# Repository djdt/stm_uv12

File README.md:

# stm_uv12

This repository cotains the kicad files and code for a UVx irradiator designed to fit over a standard 12 well plate.
The controller is powered by a single protected 18650 Li-ion cell, each row of LEDs (3 rows of 4 LEDs) has a R1218x DC/DC converter for control of LED brightness.
Approximate doses (J/m^2) have been calculated using the expected LED outputs and are delivered at a specified rate using the controller.

## PCB Files

UVA_12W_LED_CONTROL: stm32 control board with 16x2 OLED screen (16pin connector).

UVA_12W_LED: board for use with 4x VLMU1610 UVA LEDs.

UVC_12W_LED: board for use with 4x SML-LXF3535UVC UVC LEDs.

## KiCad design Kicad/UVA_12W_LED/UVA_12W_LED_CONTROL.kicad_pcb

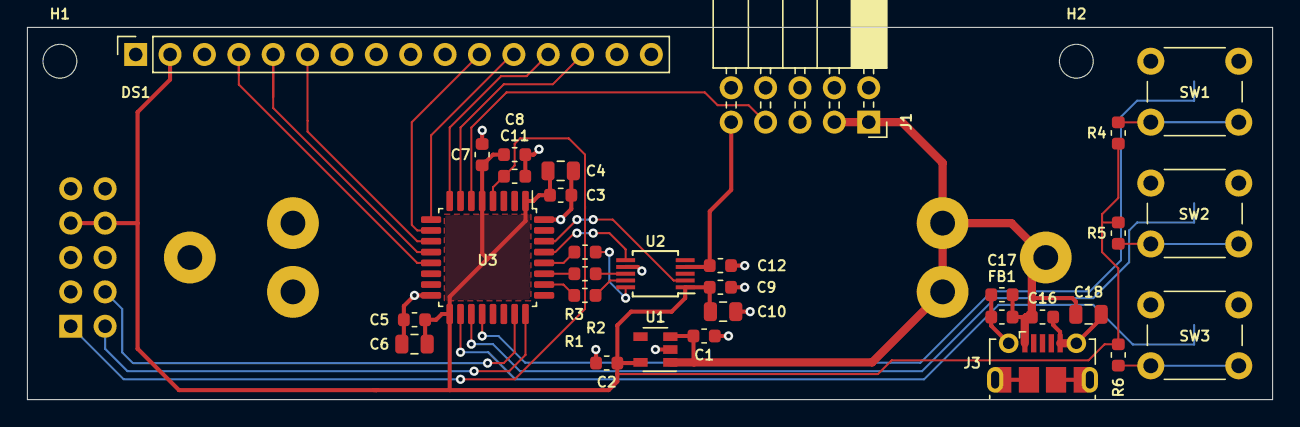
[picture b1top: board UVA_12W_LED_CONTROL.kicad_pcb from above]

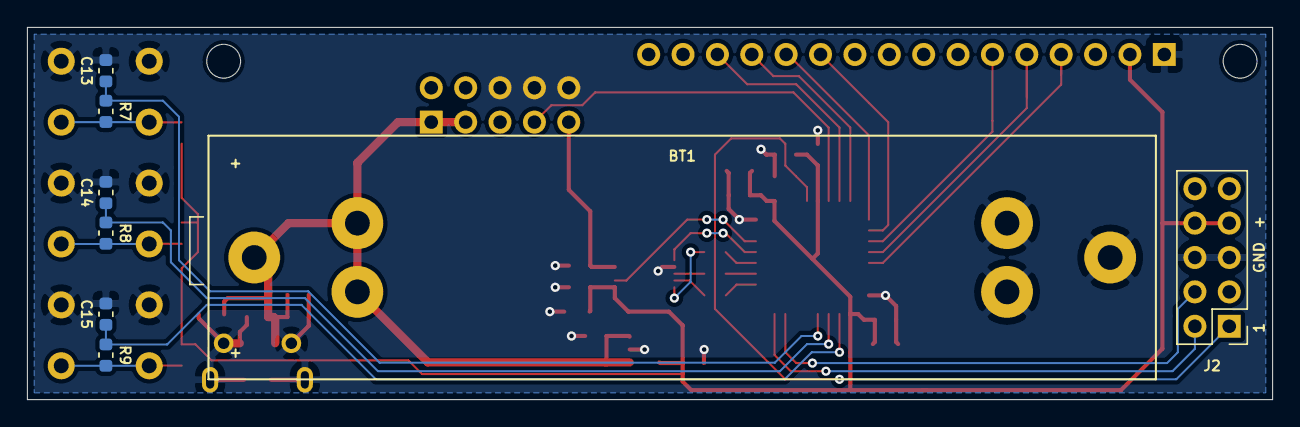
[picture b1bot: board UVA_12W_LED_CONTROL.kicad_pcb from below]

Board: 2 copper layers, 92.0 x 27.5 mm, 41 parts (8 on the bottom side), 29 nets.

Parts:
BT1: Battery; BatteryClip_18mm
C1, C2, C8: 1u; C_0603_1608Metric
C3, C5, C9, C11, C12, C17: 0u1; C_0603_1608Metric
C4, C6: 4u7; C_0805_2012Metric
C7, C13, C14, C15, C16: 10n; C_0603_1608Metric
C10, C18: 10u; C_0805_2012Metric
DS1: OLED-016N002A; PinSocket_1x16_P2.54mm_Vertical
FB1: Ferrite_Bead; L_0603_1608Metric
H1, H2: MountingHole; MountingHole_2.5mm
J1: Conn_02x05_Odd_Even; PinSocket_2x05_P2.54mm_Horizontal
J2: Conn_02x05_Odd_Even; PinHeader_2x05_P2.54mm_Vertical
J3: USB_B_Micro; USB_Micro-B_Molex-105017-0001
R1, R2, R3: 100; R_0603_1608Metric
R4, R5, R6, R7, R8, R9: 10k; R_0603_1608Metric
SW1, SW2, SW3: SW_Push; SW_PUSH_6mm
U1: MSCP1824T; SOT-23-5
U2: MCP48FVBX1; MSOP-10_3x3mm_P0.5mm
U3: STM32F042K6Tx; LQFP-32_7x7mm_P0.8mm

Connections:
/3V3: C2.1, C3.1, C4.1, C5.1, C6.1, C7.1, C8.1, C9.1, C10.1, DS1.2, J2.7, J2.8, R4.1, R5.1, R6.1, U1.5, U2.1, U3.1, U3.5, U3.17
/CS_DAC: U2.2, U3.30
/DB4: DS1.11, U3.10
/DB5: DS1.12, U3.9
/DB6: DS1.13, U3.8
/DB7: DS1.14, U3.7
/Dim: C12.1, J1.9, U2.4
/E: DS1.6, U3.11
/Enable: J1.7, U3.6
/MISO: R3.2, U2.8
/MOSI: R2.2, U3.28
/RS: DS1.4, U3.13
/RST: C11.1, J2.1, U3.4
/R~W: DS1.5, U3.12
/S1: C13.1, R7.1, U3.20
/S2: C14.1, R8.1, U3.19
/S3: C15.1, R9.1, U3.18
/SCLK: R1.2, U3.26
/SWCLK: J2.2, U3.24
/SWDIO: J2.4, U3.23
/Vbat: BT1.1, C1.1, C16.1, C17.1, C18.1, FB1.1, J1.1, J1.3, J3.1, U1.1, U1.3
/~LAT0: U2.6, U3.29
GND: BT1.2, C1.2, C2.2, C3.2, C4.2, C5.2, C6.2, C7.2, C8.2, C9.2, C10.2, C11.2, C12.2, C13.2, C14.2, C15.2, C16.2, C17.2, C18.2, DS1.1, FB1.2, J1.6, J1.8, J1.10, J2.5, J2.6, J3.5, J3.6, SW1.1, SW2.1, SW3.1, U1.2, U2.7, U3.16, U3.32
unnamed: R1.1, U2.9
unnamed: R2.1, U2.10
unnamed: R3.1, U3.27
unnamed: R4.2, R7.2, SW1.2
unnamed: R5.2, R8.2, SW2.2
unnamed: R6.2, R9.2, SW3.2

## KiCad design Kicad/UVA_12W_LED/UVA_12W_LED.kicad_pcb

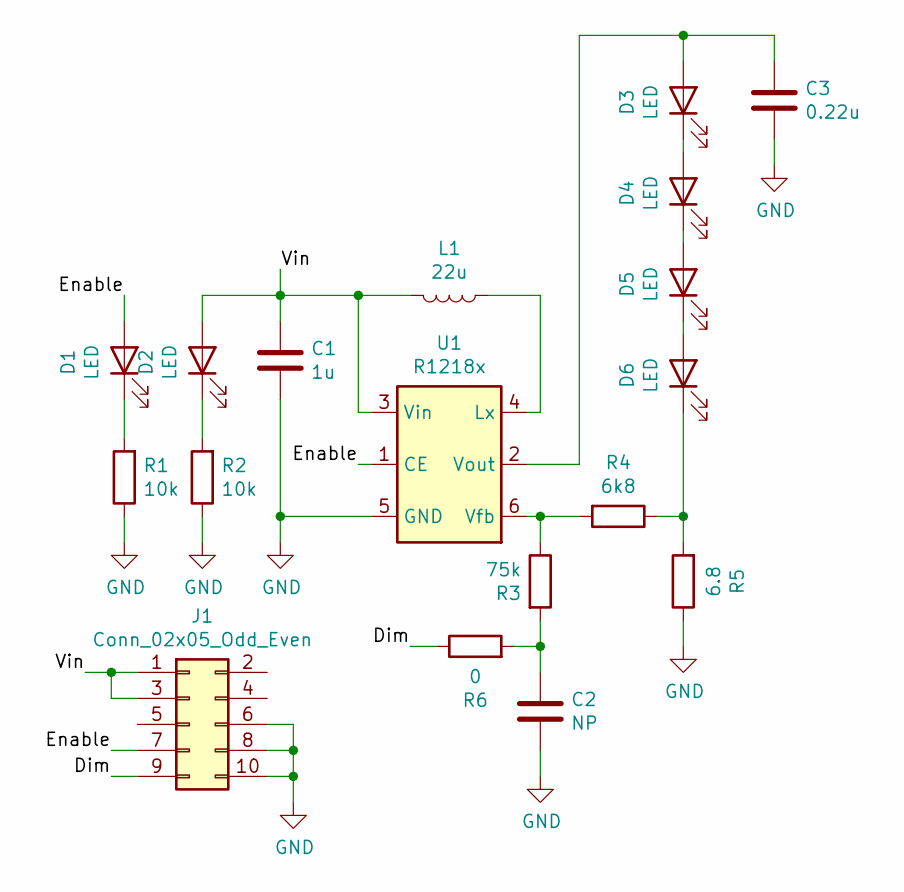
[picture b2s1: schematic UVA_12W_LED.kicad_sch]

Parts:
C1: 1u; C_0603_1608Metric
C2: NP; C_0603_1608Metric
C3: 0.22u; C_0603_1608Metric
D1, D2: LED; LED_0805_2012Metric
D3, D4, D5, D6: LED; VLMU1610
J1: Conn_02x05_Odd_Even; PinSocket_2x05_P2.54mm_Vertical_SMD
L1: 22u; L_0805_2012Metric
R1, R2: 10k; R_0603_1608Metric
R3: 75k; R_0603_1608Metric
R4: 6k8; R_0603_1608Metric
R5: 6.8; R_0603_1608Metric
R6: 0; R_0603_1608Metric
U1: R1218x; SOT-23-6

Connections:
/Dim: J1.9, R6.1
/Enable: D1.2 (A), J1.7, U1.1 (CE)
/Vin: C1.1, D2.2 (A), J1.1, J1.3, L1.2, U1.3 (Vin)
GND: C1.2, C2.2, C3.2, J1.6, J1.8, J1.10, R1.1, R2.1, R5.1, U1.5 (GND)
unnamed: C2.1, R3.2, R6.2
unnamed: C3.1, D3.2 (A), U1.2 (Vout)
unnamed: D1.1 (K), R1.2
unnamed: D2.1 (K), R2.2
unnamed: D3.1 (K), D4.2 (A)
unnamed: D4.1 (K), D5.2 (A)
unnamed: D5.1 (K), D6.2 (A)
unnamed: D6.1 (K), R4.1, R5.2
unnamed: L1.1, U1.4 (Lx)
unnamed: R3.1, R4.2, U1.6 (Vfb)

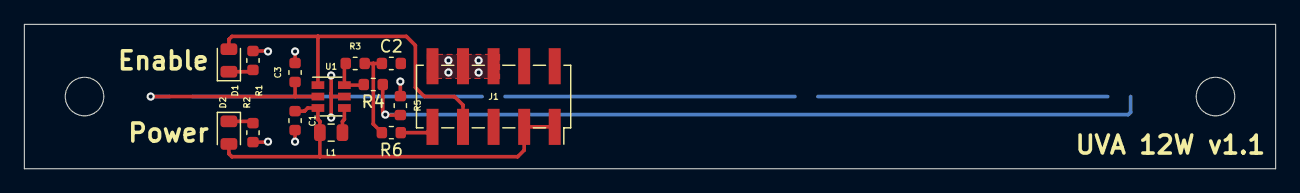
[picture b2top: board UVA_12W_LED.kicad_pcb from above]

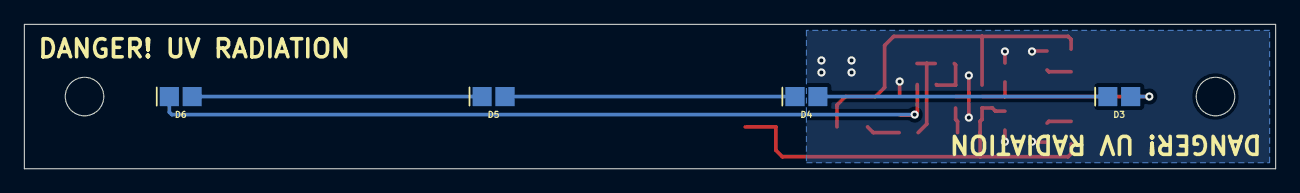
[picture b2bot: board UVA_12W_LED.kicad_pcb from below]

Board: 2 copper layers, 104.0 x 12.0 mm, 18 parts (4 on the bottom side), 14 nets.

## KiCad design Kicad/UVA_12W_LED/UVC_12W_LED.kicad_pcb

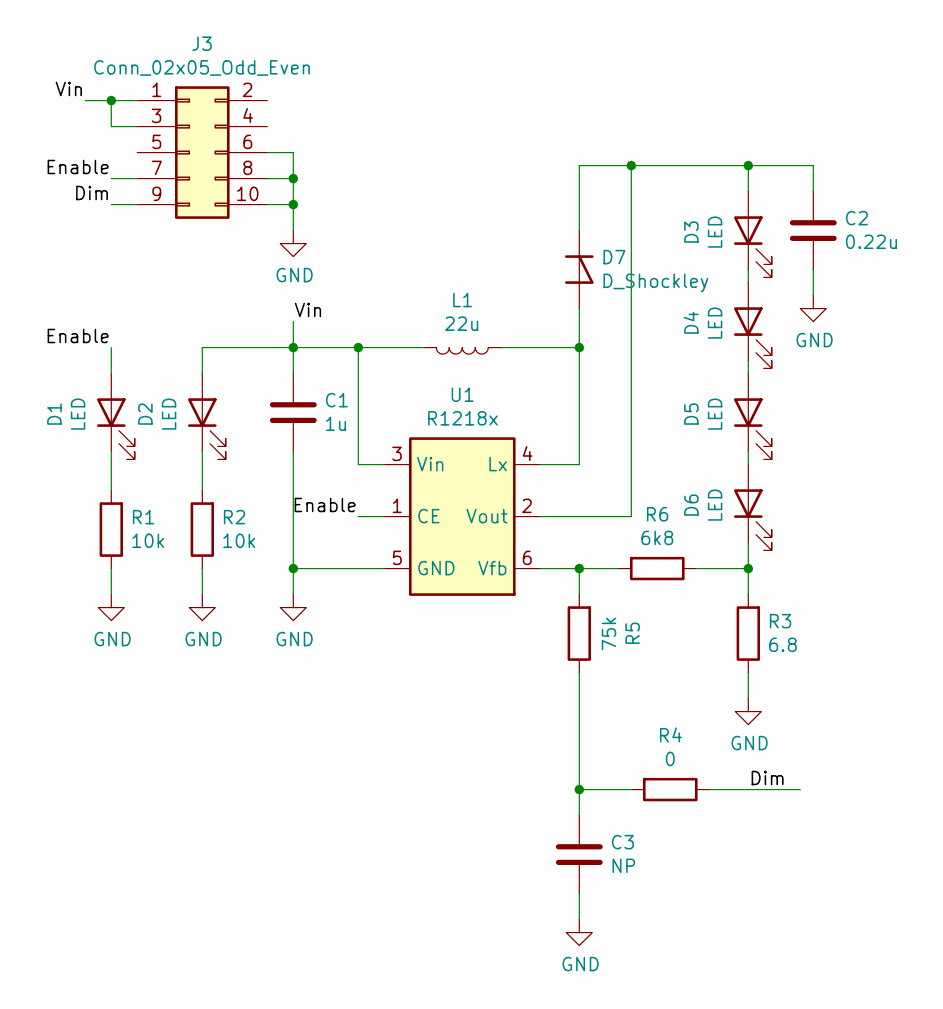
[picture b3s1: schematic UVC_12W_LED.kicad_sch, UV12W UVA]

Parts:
C1: 1u; C_0603_1608Metric
C2: 0.22u; C_0603_1608Metric
C3: NP; C_0603_1608Metric
D1, D2: LED; LED_0805_2012Metric
D3, D4, D5, D6: LED; SML-LXF3535UVC
D7: D_Shockley; D_SOD-123F
J3: Conn_02x05_Odd_Even; PinSocket_2x05_P2.54mm_Vertical_SMD
L1: 22u; L_Taiyo-Yuden_NR-30xx_HandSoldering
R1, R2: 10k; R_0603_1608Metric
R3: 6.8; R_0603_1608Metric
R4: 0; R_0603_1608Metric
R5: 75k; R_0603_1608Metric
R6: 6k8; R_0603_1608Metric
U1: R1218x; SOT-23-6

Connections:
/Dim: J3.9, R4.1
/Enable: D1.2 (A), J3.7, U1.1 (CE)
/Vin: C1.1, D2.2 (A), J3.1, J3.3, L1.2, U1.3 (Vin)
GND: C1.2, C2.2, C3.2, J3.6, J3.8, J3.10, R1.1, R2.1, R3.1, U1.5 (GND)
unnamed: C2.1, D3.2 (A), D7.1 (K), U1.2 (Vout)
unnamed: C3.1, R4.2, R5.1
unnamed: D1.1 (K), R1.2
unnamed: D2.1 (K), R2.2
unnamed: D3.1 (K), D4.2 (A)
unnamed: D4.1 (K), D5.2 (A)
unnamed: D5.1 (K), D6.2 (A)
unnamed: D6.1 (K), R3.2, R6.1
unnamed: D7.2 (A), L1.1, U1.4 (Lx)
unnamed: R5.2, R6.2, U1.6 (Vfb)

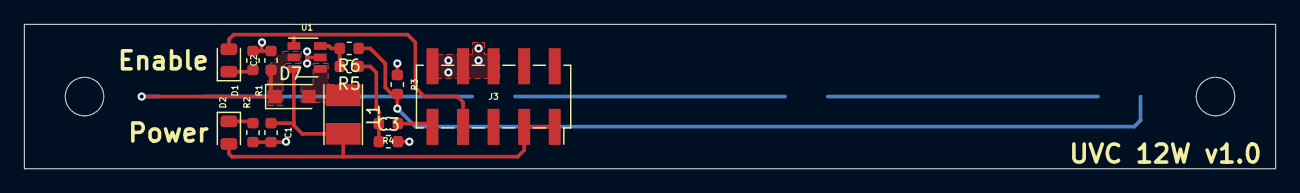
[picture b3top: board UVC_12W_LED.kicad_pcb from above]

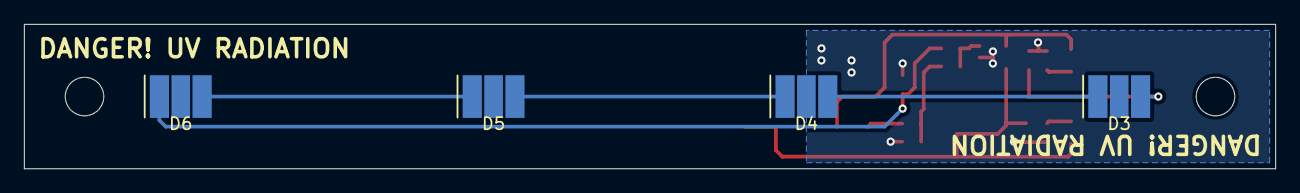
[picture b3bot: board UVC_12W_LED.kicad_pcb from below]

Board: 2 copper layers, 104.0 x 12.0 mm, 19 parts (4 on the bottom side), 14 nets.

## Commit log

2020-10-11 initial
2020-10-13 fix registers
2020-10-13 return val, fix cs and lat
2020-10-22 add buttons
2020-10-22 fix buttons
2020-10-22 added timer based repeat on hold
2020-10-24 printing of EFD
2020-10-24 use a mask for updates, redid display printing
2020-10-24 speed up buttons, efd prints correctly
2020-11-01 countdown mode is better
2020-11-01 more countdown
2020-11-02 gelp
2020-11-02 add printing funcs
2020-11-02 custom prediv clock for 40kHz
2020-11-02 tidy
2020-11-02 everything works nicely
2020-11-04 clean up read / write, add cgram access for custom chars
2020-11-04 add animation frames
2020-11-04 use [s] for completed symbol
2020-11-04 use [p] for paused
2020-11-04 added animation for cell
2020-11-04 fix pad
2020-11-07 remove animation
2020-11-14 0J mode for endless;2u
2020-12-01 new max rates
2020-12-08 ale fix
2020-12-08 stepsize options
2020-12-08 dose units everywhere, new time prints hours too
2021-03-16 better defaults
2022-01-23 added kicad files for PCBs
